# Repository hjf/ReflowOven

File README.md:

# ESP8266 Reflow Oven Controller
*Instrucciones en español mas abajo*
## Introduction

This is a simple PID controller with a web interface for a reflow oven. It requires a MAX31856, a K-type thermocouple, a MOC3041 optotriac, a suitable triac for your mains voltage, and a ESP-12E module. 

### Software

The Arduino-based firmware is included. It requres tzapu's [WiFiManager](https://github.com/tzapu/WiFiManager) to set up. It also includes ArduinoOTA for remote firmware upgrades.

### Hardware

The KiCAD files are available too, but this is a simple circuit that can, obviously, be built out of standard arduino modules. Instead of the triac and optotriac, a SSR (Solid State Relay) can be used. A mechanical relay cannot be used as this circuit switches the load several times per second for accurate temperature control.

---

## Introducción

Este es un controlador PID muy simple, con una interfaz web, para controlar un horno de soldadura por refusion. Necesita un MAX31856, una termocupla tipo K, un optotriac MOC3041, un triac adecuado para tu voltaje de linea, y un modulo ESP-12E

### Software

Se incluye el firmware basado en Arduino. Necesita la libreria [WiFiManager](https://github.com/tzapu/WiFiManager) de tzapu para la configuracion. Tambien incluye ArduinoOTA para actualizaciones remotas.

### Hardware

También se incluyen los archivos de KiCAD, pero este es un circuito tan simple que obviamente se puede armar con modulos Arduino comunes. En lugar del triac y optotriac, se puede usar un modulo SSR. No es posible usar un relay mecánico ya que el circuito conmuta la salida varias veces por segundo para un control preciso de la temperatura.

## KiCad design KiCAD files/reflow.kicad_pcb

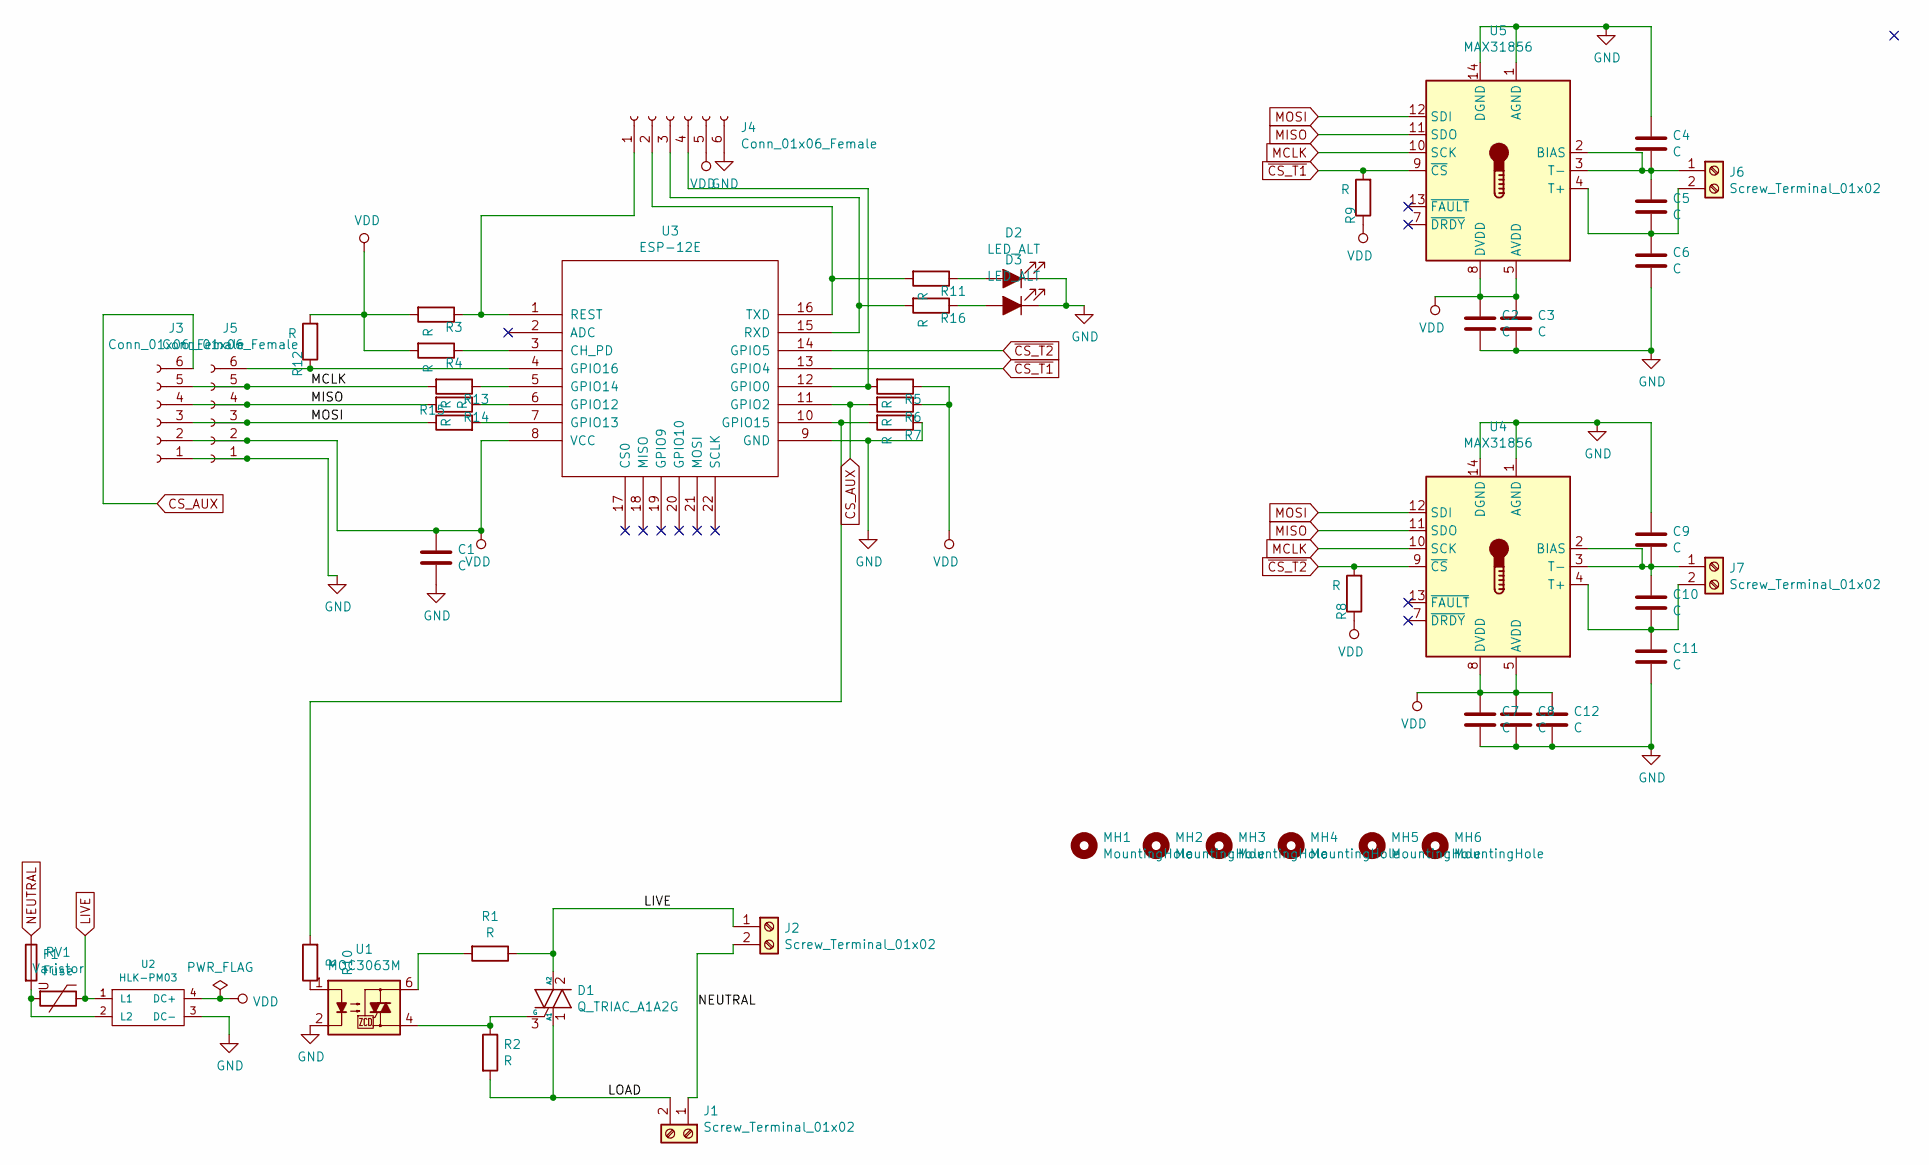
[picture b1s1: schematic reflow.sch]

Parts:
C1: C; CP_Tantalum_Case-C_EIA-6032-28_Hand
C2, C3, C4, C5, C6, C7, C8, C9, C10, C11, C12: C; R_0805
D1: Q_TRIAC_A1A2G; to220_std_14cw
D2, D3: LED_ALT; LED_0805_HandSoldering
F1: Fuse; FC-211
J1, J2, J6, J7: Screw_Terminal_01x02; mkds_1,5-2
J3, J4, J5: Conn_01x06_Female; Pin_Header_Straight_1x06_Pitch2.54mm
MH1, MH2, MH3, MH4, MH5, MH6: MountingHole; MountingHole_3.2mm_M3
R1, R2: R; R_Axial_DIN0207_L6.3mm_D2.5mm_P10.16mm_Horizontal
R3, R4, R5, R6, R7, R8, R9, R10, R11, R12, R13, R14, R15, R16: R; R_0805
RV1: Varistor; RV_Disc_D12_W3.9_P7.5
U1: MOC3063M; DIP-6_W7.62mm
U2: HLK-PM03
U3: ESP-12E; ESP-12E_SMD
U4, U5: MAX31856; TSSOP-14_4.4x5mm_Pitch0.65mm

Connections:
/LOAD: D1.1 (A1), J1.2, R2.2
CS_AUX: J3.6, R6.2, U3.11 (GPIO2)
GND: C1.2, C2.2, C3.2, C4.1, C6.2, C7.2, C8.2, C9.1, C11.2, C12.2, D2.1 (K), D3.1 (K), J3.1, J4.6, J5.1, R7.1, U1.2, U2.3 (DC-), U3.9 (GND), U4.1 (AGND), U4.14 (DGND), U5.1 (AGND), U5.14 (DGND)
LIVE: D1.2 (A2), J2.1, R1.1, RV1.1, U2.1 (L1)
MCLK: J3.5, J5.5, R13.2, U4.10 (SCK), U5.10 (SCK)
MISO: J3.4, J5.4, R14.2, U4.11 (SDO), U5.11 (SDO)
MOSI: J3.3, J5.3, R15.1, U4.12 (SDI), U5.12 (SDI)
NEUTRAL: F1.1, J1.1, J2.2
unnamed: C4.2, C5.1, J6.1, U5.2 (BIAS), U5.3 (T-)
unnamed: C5.2, C6.1, J6.2, U5.4 (T+)
unnamed: C9.2, C10.1, J7.1, U4.2 (BIAS), U4.3 (T-)
unnamed: C10.2, C11.1, J7.2, U4.4 (T+)
unnamed: D1.3 (G), R2.1, U1.4
unnamed: D2.2 (A), R11.1
unnamed: D3.2 (A), R16.1
unnamed: F1.2, RV1.2, U2.2 (L2)
unnamed: J4.1, R3.1, U3.1 (REST)
unnamed: J4.2, R11.2, U3.16 (TXD)
unnamed: J4.3, R16.2, U3.15 (RXD)
unnamed: J4.4, R5.2, U3.12 (GPIO0)
unnamed: J5.6, R12.1, U3.4 (GPIO16)
unnamed: R1.2, U1.6
unnamed: R4.1, U3.3 (CH_PD)
unnamed: R10.1, U1.1
unnamed: R7.2, R10.2, U3.10 (GPIO15)
unnamed: R13.1, U3.5 (GPIO14)
unnamed: R14.1, U3.6 (GPIO12)
unnamed: R15.2, U3.7 (GPIO13)
VDD: C1.1, C2.1, C3.1, C7.1, C8.1, C12.1, J3.2, J4.5, J5.2, R3.2, R4.2, R5.1, R6.1, R8.1, R9.1, R12.2, U2.4 (DC+), U3.8 (VCC), U4.5 (AVDD), U4.8 (DVDD), U5.5 (AVDD), U5.8 (DVDD)
~CS_T1: R9.2, U3.13 (GPIO4), U5.9 (~CS)
~CS_T2: R8.2, U3.14 (GPIO5), U4.9 (~CS)

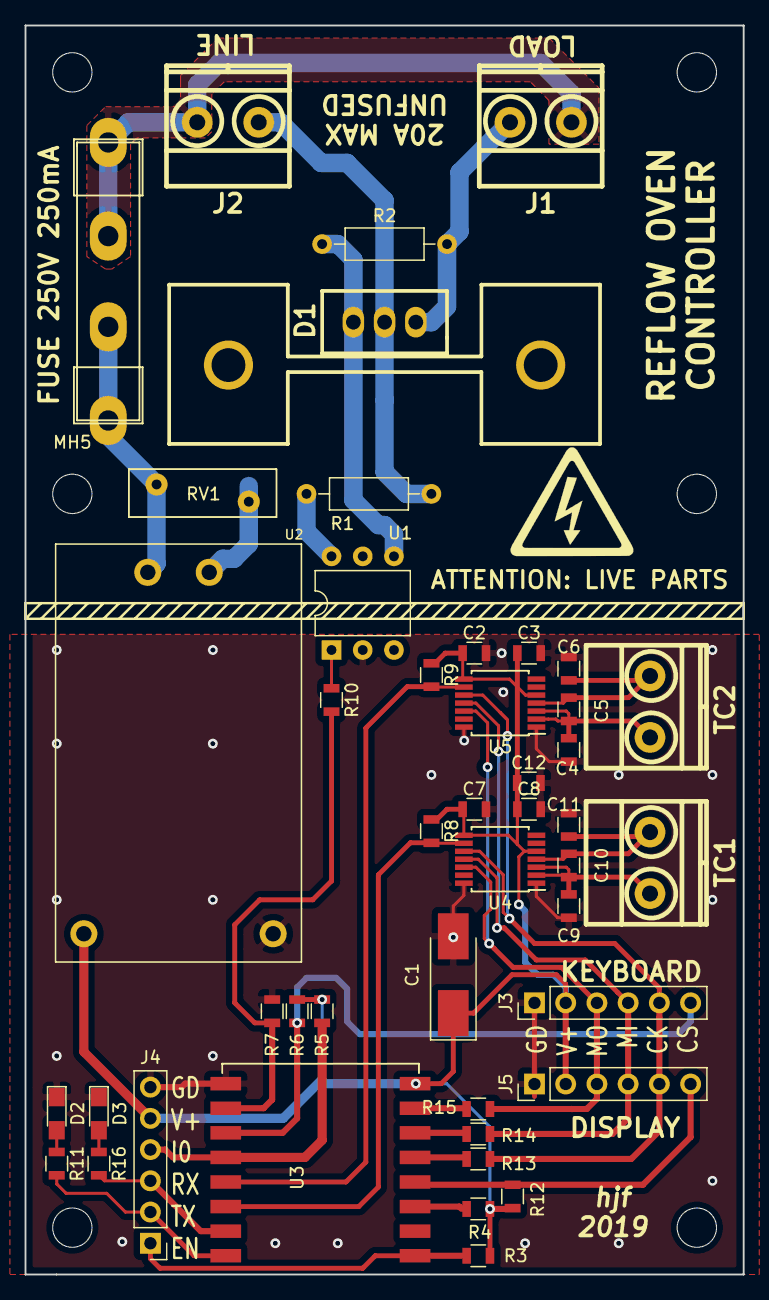
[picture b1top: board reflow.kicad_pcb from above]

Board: 2 copper layers, 58.4 x 101.6 mm, 51 parts (0 on the bottom side), 31 nets.

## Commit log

2021-02-15 Initial
2021-02-15 fix triac direction
2021-02-15 deleted outdated gerbers
2021-02-15 added firmware
